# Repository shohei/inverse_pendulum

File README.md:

# Inverse pendulum

- Espr developer(ESP-WROOM-02 module)
- MPU6050 (6DOF accelerometer and gyro)
- TA7291P (H bridge motor driver)

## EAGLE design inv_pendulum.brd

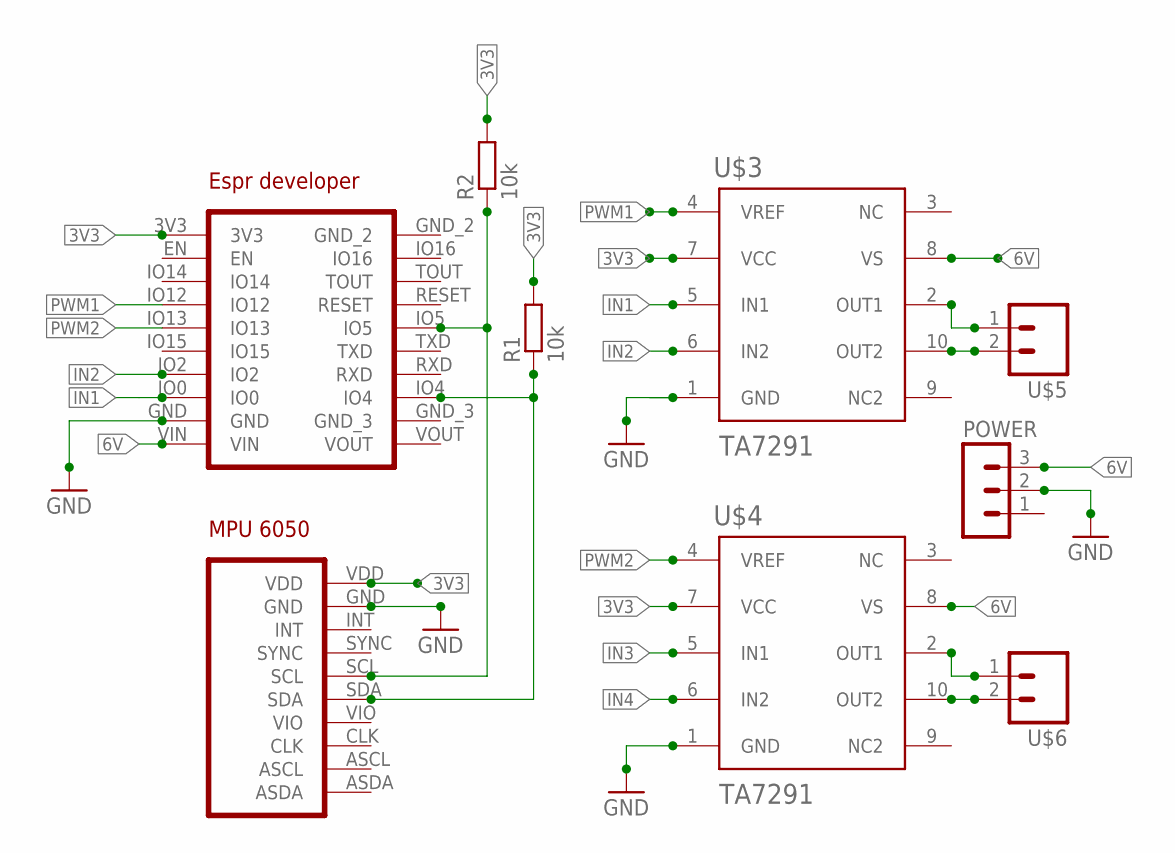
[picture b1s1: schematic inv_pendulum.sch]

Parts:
POWER: MA03-1
R1, R2: 10k; 0204/7
U$1: MPU6050
U$2: ESPR_DEVELOPER; ESPR_DEV
U$3, U$4: TA7291; HSIP10
U$5, U$6: M02LOCK_LONGPADS; 1X02_LOCK_LONGPADS

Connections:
3V3: R1.2, R2.2, U$1.VDD, U$2.3V3, U$3.7 (VCC), U$4.7 (VCC)
6V: POWER.3, U$2.VIN, U$3.8 (VS), U$4.8 (VS)
GND: POWER.2, U$1.GND, U$2.GND, U$3.1 (GND), U$4.1 (GND)
IN1: U$2.IO0, U$3.5 (IN1)
IN2: U$2.IO2, U$3.6 (IN2)
IN3: U$4.5 (IN1)
IN4: U$4.6 (IN2)
unnamed: U$3.2 (OUT1), U$5.1
unnamed: U$3.10 (OUT2), U$5.2
unnamed: U$4.2 (OUT1), U$6.1
unnamed: U$4.10 (OUT2), U$6.2
PWM1: U$2.IO12, U$3.4 (VREF)
PWM2: U$2.IO13, U$4.4 (VREF)
SCL: R2.1, U$1.SCL, U$2.IO5
SDA: R1.1, U$1.SDA, U$2.IO4

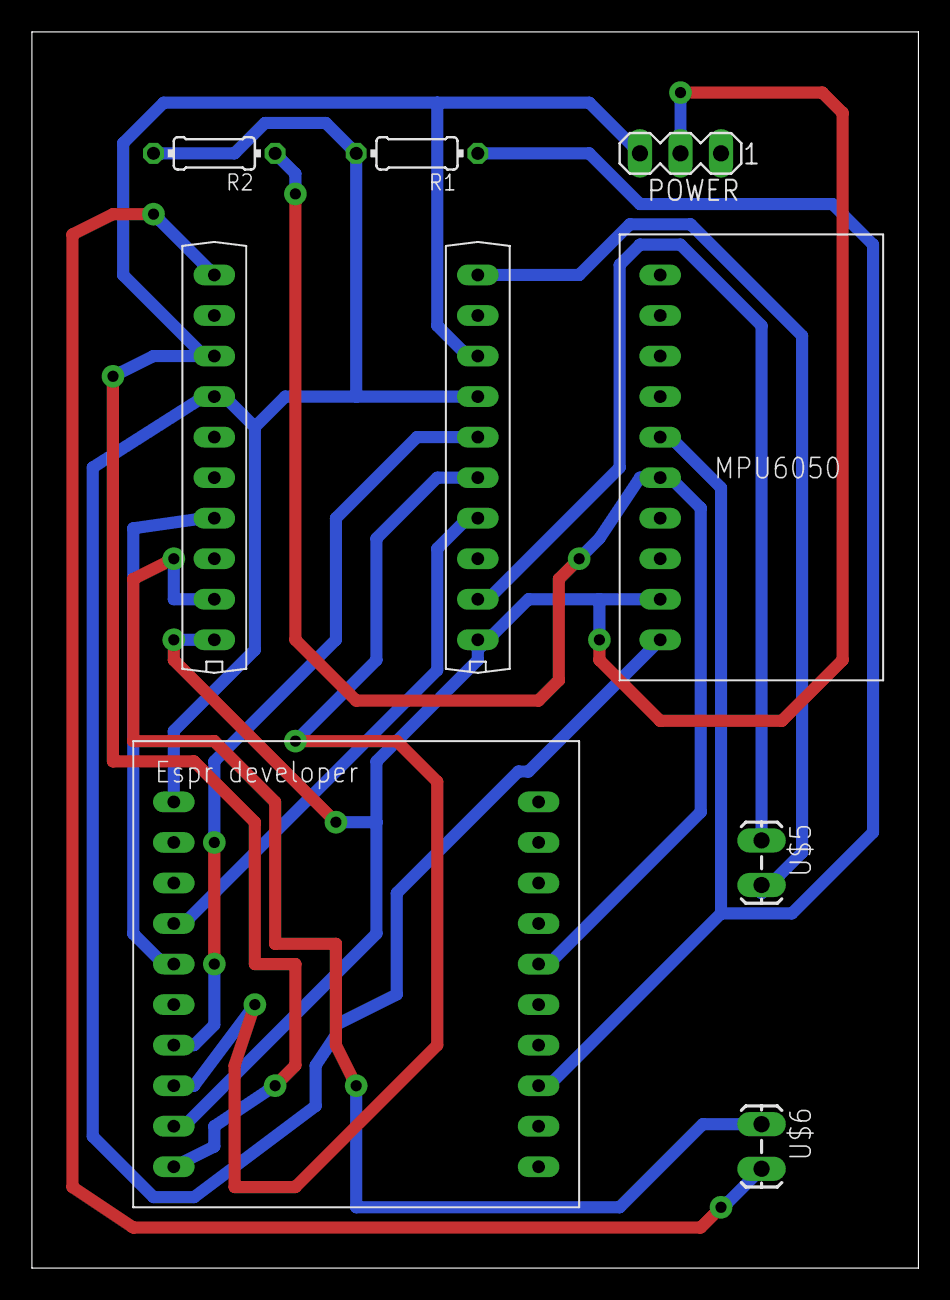
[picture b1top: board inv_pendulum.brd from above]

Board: 2 copper layers, 55.5 x 77.5 mm, 9 parts (0 on the bottom side), 13 nets.

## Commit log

2016-11-09 add .gitignore
2016-11-09 add readme
2016-11-09 add schematics image
2016-11-09 add image
2016-12-14 update design
2016-12-14 fix readme

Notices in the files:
parts and their libraries:
SparkFun-Connectors: Licensing: Creative Commons ShareAlike 4.0 International - https://creativecommons.org/licenses/by-sa/4.0
